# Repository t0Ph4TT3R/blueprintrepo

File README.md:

# My HackPad
My HackPad consists of 9 buttons that I will use as shortcuts in the game developing app Godot!

This was my first time ever using KiCad or anything of the sort, so I was able to learn a lot about how PCBs are made!

Schematic

PCB

I used OnShape as my software for cadding the case for the PCB, and I have had prior experience to cadding before this, however, this was my first time importing DXF files into CAD software.

For the coding aspect, I used python because I am familiar with it, however I still needed to google some things about the library and how to use it accordingly.

***Specifications***
BOM:

9x Cherry MX Switches
2x SK6812 MINI Leds
1x XIAO RP2040
9x Blank DSA Keycaps (I want to try and 3d print these myself)
4x M3x16 Bolt
4x M3 Heatset

Others:

KMK Firmware
Top.3mf (I want to try and 3d print these myself)
Bottom.3mf (I want to try and 3d print these myself)

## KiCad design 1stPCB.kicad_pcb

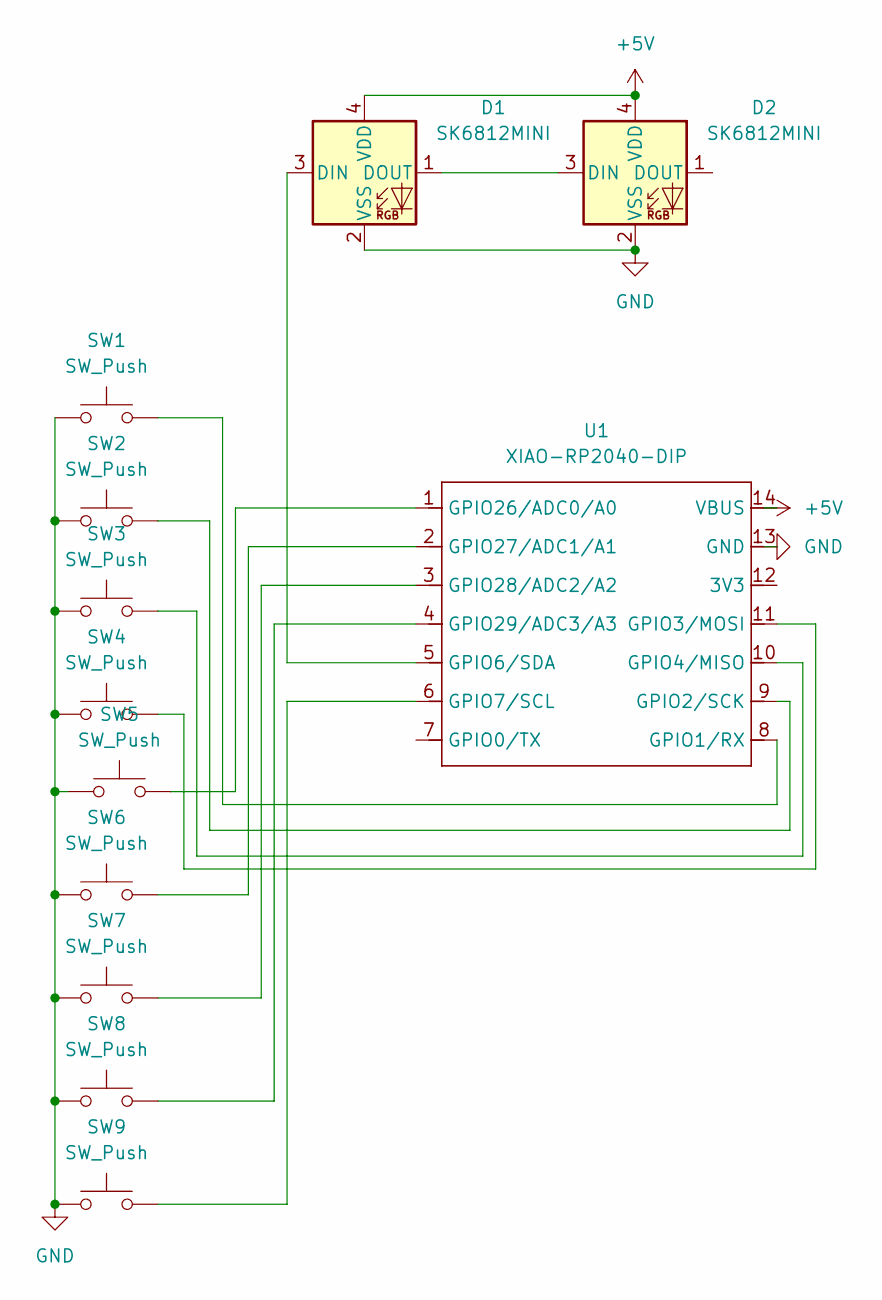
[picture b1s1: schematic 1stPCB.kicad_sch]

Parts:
D1, D2: SK6812MINI; LED_SK6812MINI_PLCC4_3.5x3.5mm_P1.75mm
SW1, SW2, SW3, SW4, SW5, SW6, SW7, SW8, SW9: SW_Push; SW_Cherry_MX_1.00u_PCB
U1: XIAO-RP2040-DIP

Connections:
+5V: D1.4 (VDD), D2.4 (VDD), U1.14 (VBUS)
GND: D1.2 (VSS), D2.2 (VSS), SW1.1, SW2.1, SW3.1, SW4.1, SW5.1, SW6.1, SW7.1, SW8.1, SW9.1, U1.13 (GND)
unnamed: D1.3 (DIN), U1.5 (GPIO6/SDA)
unnamed: D1.1 (DOUT), D2.3 (DIN)
unnamed: SW1.2, U1.8 (GPIO1/RX)
unnamed: SW2.2, U1.9 (GPIO2/SCK)
unnamed: SW4.2, U1.11 (GPIO3/MOSI)
unnamed: SW3.2, U1.10 (GPIO4/MISO)
unnamed: SW9.2, U1.6 (GPIO7/SCL)
unnamed: SW5.2, U1.1 (GPIO26/ADC0/A0)
unnamed: SW6.2, U1.2 (GPIO27/ADC1/A1)
unnamed: SW7.2, U1.3 (GPIO28/ADC2/A2)
unnamed: SW8.2, U1.4 (GPIO29/ADC3/A3)

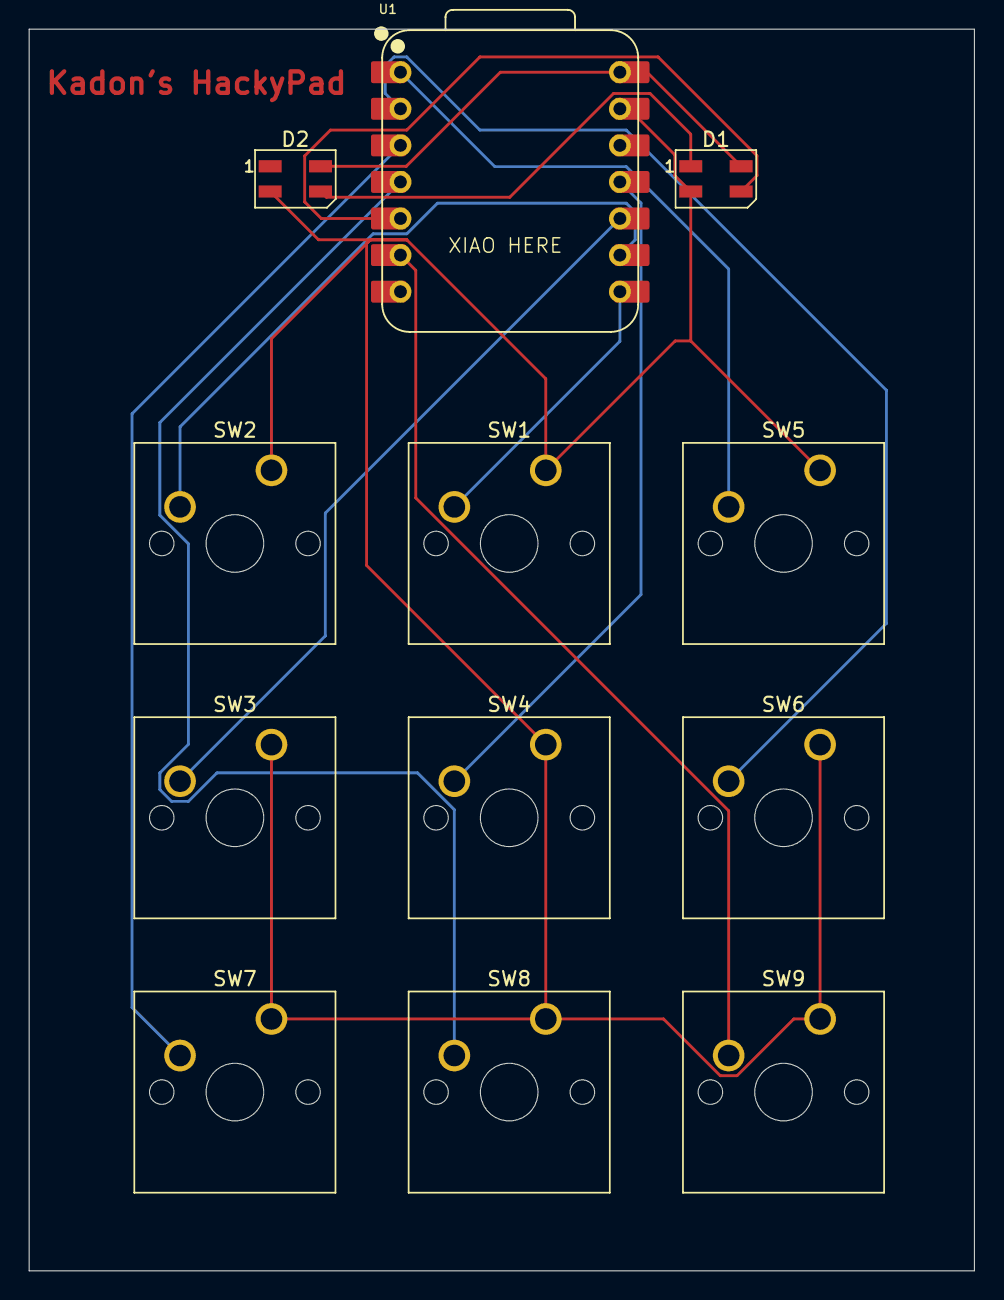
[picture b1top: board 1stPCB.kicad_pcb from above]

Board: 2 copper layers, 65.6 x 86.2 mm, 12 parts (0 on the bottom side), 13 nets.

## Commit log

2025-11-19 Add files via upload
    These are my cad files for my MacroPad made in OnShape.
2025-11-20 Add files via upload
    These are my HackyPad PCB files made in KiCad with nine buttons!
2025-11-20 Create HackyPad.py
    This is the first iteration of the python code, and I will later try and find out more about how the key mapping and pressing work.
2025-11-21 Add files via upload
    These are the part and assembly with the PCB part.
2025-11-21 Delete Assembly 1.3mf
    Old Assembly without PCB
2025-11-21 Create test
2025-11-21 Create test1
